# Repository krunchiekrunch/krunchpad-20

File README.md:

# krunchpad-20
A 20 key macro pad powered by RP2040 with KMK

Featuring an open-top design from the case and an OLED display for displaying key map.

# Images

| PCB | 3D Preview | Case |
|-----|------------|------|
|  |  |  |
| |  | |

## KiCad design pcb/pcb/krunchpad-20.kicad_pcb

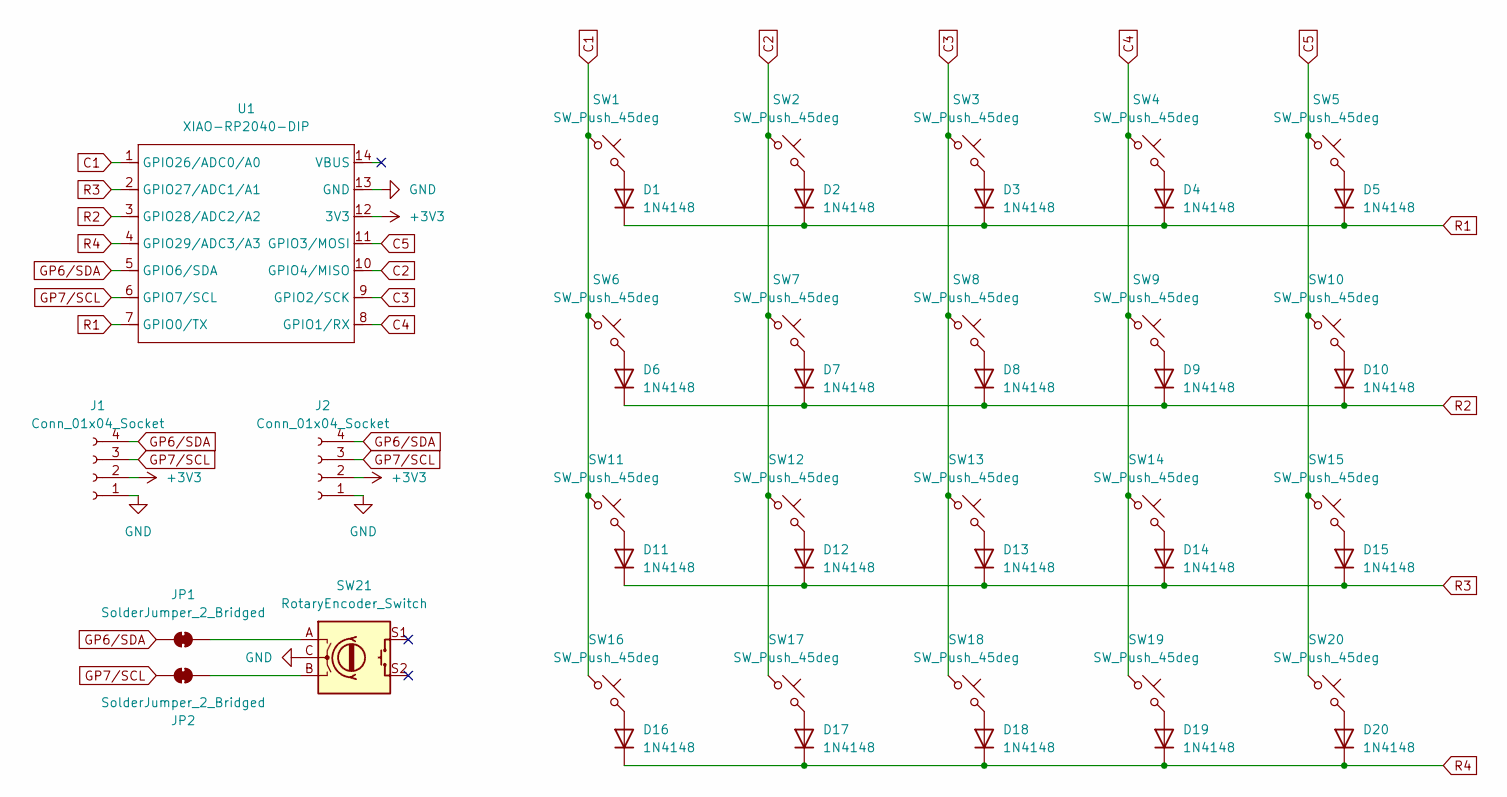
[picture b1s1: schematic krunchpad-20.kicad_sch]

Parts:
D1, D2, D3, D4, D5, D6, D7, D8, D9, D10, D11, D12, D13, D14, D15, D16, D17, D18, D19, D20: 1N4148; D_DO-35_SOD27_P7.62mm_Horizontal
J1, J2: Conn_01x04_Socket; PinSocket_1x04_P2.54mm_Vertical_SMD_Pin1Left
JP1, JP2: SolderJumper_2_Bridged; SolderJumper-2_P1.3mm_Bridged_RoundedPad1.0x1.5mm
SW1, SW2, SW3, SW4, SW5, SW6, SW7, SW8, SW9, SW10, SW11, SW12, SW13, SW14, SW15, SW16, SW17, SW18, SW19, SW20: SW_Push_45deg; dual-hotswap_MX
SW21: RotaryEncoder_Switch; RotaryEncoder_Alps_EC11E-Switch_Vertical_H20mm
U1: XIAO-RP2040-DIP

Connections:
+3V3: J1.2, J2.2, U1.12 (3V3)
C1: SW1.1, SW6.1, SW11.1, SW16.1, U1.1 (GPIO26/ADC0/A0)
C2: SW2.1, SW7.1, SW12.1, SW17.1, U1.10 (GPIO4/MISO)
C3: SW3.1, SW8.1, SW13.1, SW18.1, U1.9 (GPIO2/SCK)
C4: SW4.1, SW9.1, SW14.1, SW19.1, U1.8 (GPIO1/RX)
C5: SW5.1, SW10.1, SW15.1, SW20.1, U1.11 (GPIO3/MOSI)
GND: J1.1, J2.1, SW21.C, U1.13 (GND)
GP6/SDA: J1.4, J2.4, JP1.1 (A), U1.5 (GPIO6/SDA)
GP7/SCL: J1.3, J2.3, JP2.2 (B), U1.6 (GPIO7/SCL)
unnamed: D1.2 (A), SW1.2
unnamed: D2.2 (A), SW2.2
unnamed: D3.2 (A), SW3.2
unnamed: D4.2 (A), SW4.2
unnamed: D5.2 (A), SW5.2
unnamed: D6.2 (A), SW6.2
unnamed: D7.2 (A), SW7.2
unnamed: D8.2 (A), SW8.2
unnamed: D9.2 (A), SW9.2
unnamed: D10.2 (A), SW10.2
unnamed: D11.2 (A), SW11.2
unnamed: D12.2 (A), SW12.2
unnamed: D13.2 (A), SW13.2
unnamed: D14.2 (A), SW14.2
unnamed: D15.2 (A), SW15.2
unnamed: D16.2 (A), SW16.2
unnamed: D17.2 (A), SW17.2
unnamed: D18.2 (A), SW18.2
unnamed: D19.2 (A), SW19.2
unnamed: D20.2 (A), SW20.2
unnamed: JP1.2 (B), SW21.A
unnamed: JP2.1 (A), SW21.B
R1: D1.1 (K), D2.1 (K), D3.1 (K), D4.1 (K), D5.1 (K), U1.7 (GPIO0/TX)
R2: D6.1 (K), D7.1 (K), D8.1 (K), D9.1 (K), D10.1 (K), U1.3 (GPIO28/ADC2/A2)
R3: D11.1 (K), D12.1 (K), D13.1 (K), D14.1 (K), D15.1 (K), U1.2 (GPIO27/ADC1/A1)
R4: D16.1 (K), D17.1 (K), D18.1 (K), D19.1 (K), D20.1 (K), U1.4 (GPIO29/ADC3/A3)

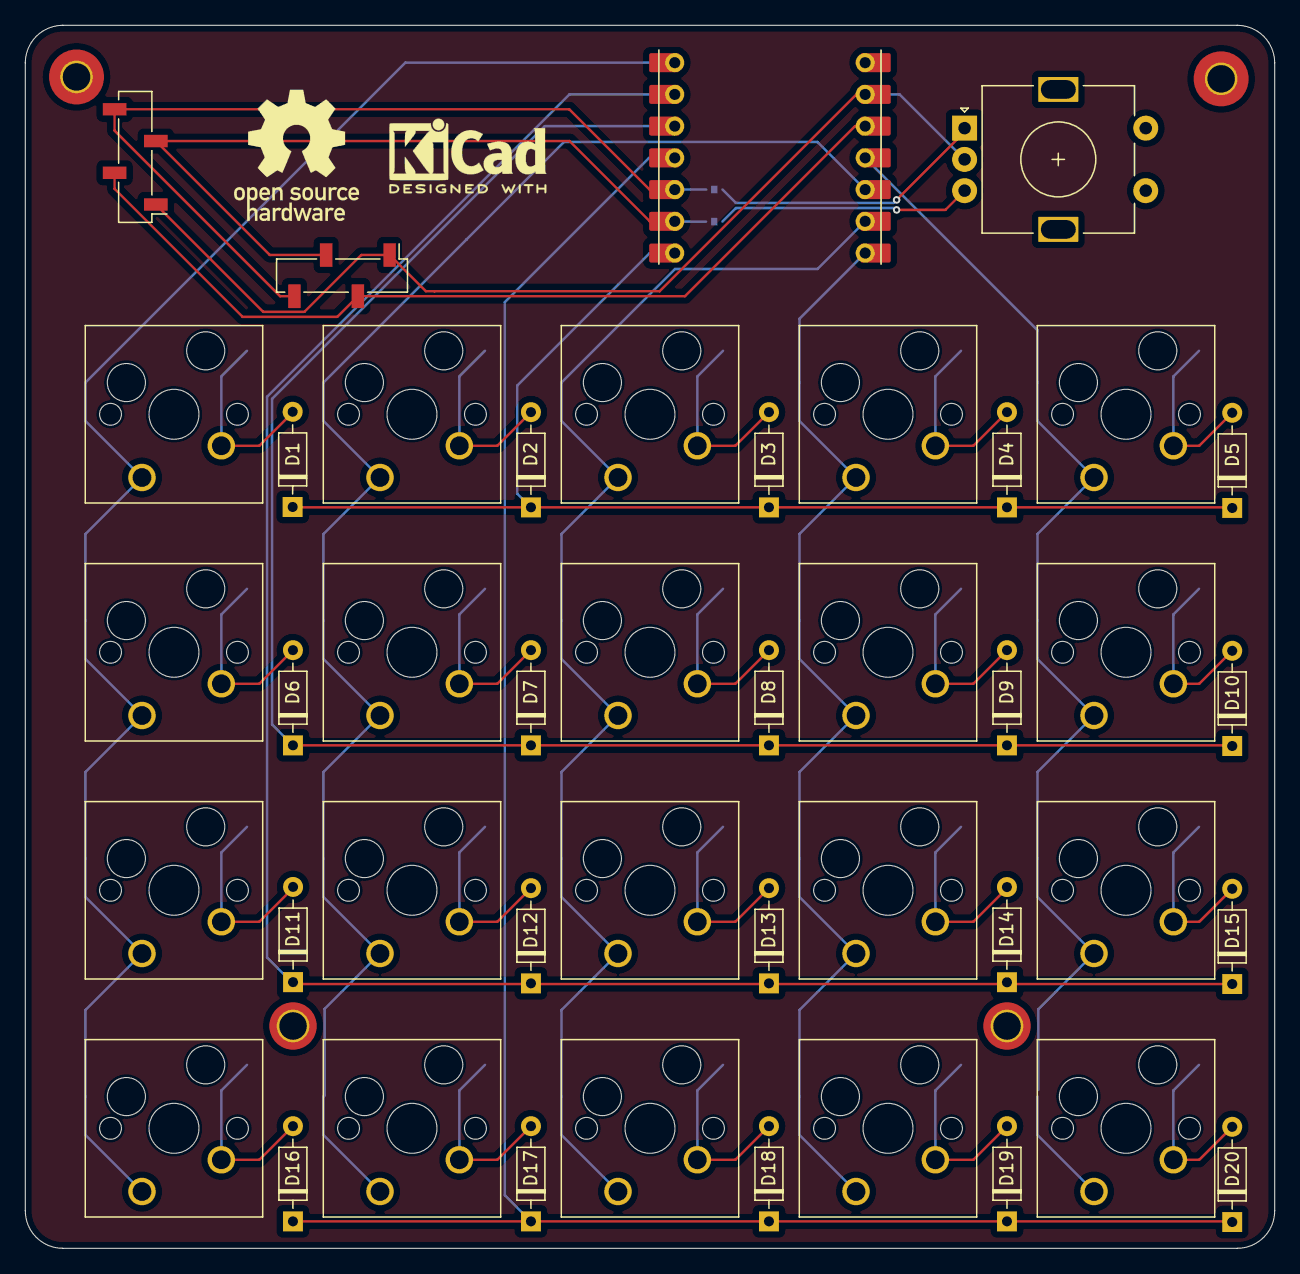
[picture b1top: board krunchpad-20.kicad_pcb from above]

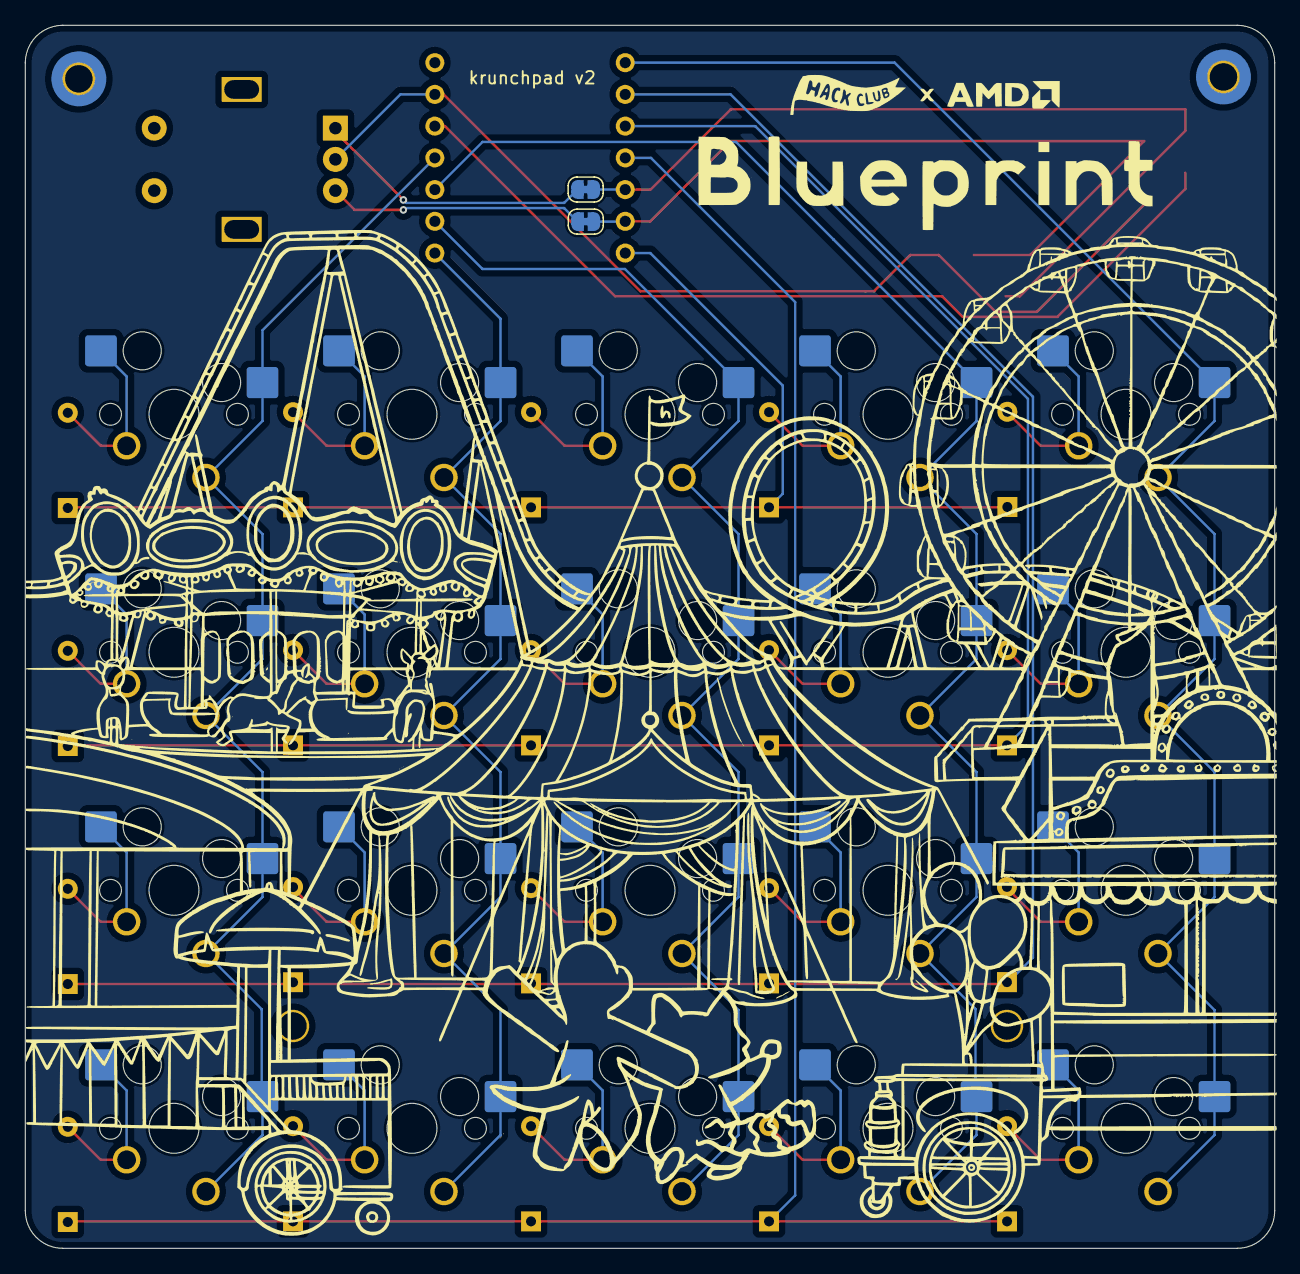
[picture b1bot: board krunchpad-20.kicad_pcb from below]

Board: 2 copper layers, 100.0 x 97.9 mm, 47 parts (2 on the bottom side), 35 nets.

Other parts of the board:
logo1: KiCad-Logo2_5mm_SilkScreen

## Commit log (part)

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2025-11-11 pcb file, cad, docs, firmware
2025-11-11 case updated to fit better
2025-11-12 BOM Update
2025-11-13 case image
2025-11-15 Changed oled socket to SMD, added extra slot for 128x64 oled, updated relevent info info in BOM, updated images
2025-11-20 updated 3d render image
2025-11-20 Fix image tag in README.md
    Updated image tag for better display of an uploaded image.
2025-12-04 updated pcb file with rotary encoder, updated gerber and case
2025-12-04 updated assets
2026-01-23 build image
2026-01-28 changed layout to numpad, added encoder support, disabled oled
